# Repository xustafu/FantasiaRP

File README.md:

# FantasiaRP
Fantasia para RP2350B

## Installation Steps:  

  * Install free [VSCode](https://code.visualstudio.com/download).  
  * Add the free [PlatformIO extension](https://marketplace.visualstudio.com/items?itemName=platformio.platformio-ide). 
  * Download this repo
  * Open it up with VSCode
  * Click the platformio compile + upload button
  * That's it!

Change pin numbers for Serial(UART), SPI, Wire(i2c...) and LED(pixels)  in your pins_arduino.h file.  
In utils.hpp, initialize objects, some of them need pins numbers like 7Segment or buttons.  
Enjoy :)

## Pony Env (Beta 3) pin map

Traced from `RP2350B+PCM5100_Template/B3Kicad/Pony_env_B3.kicad_sch`. All definitions live in `src/utils.hpp`.

| Control | GPIO | Notes |
|---|---|---|
| ATTACK slider + CV | 47 (A7) | analog, inverting summing stage |
| DECAY slider + CV | 46 (A6) | analog |
| SPEED pot + LVL CV | 45 (A5) | analog |
| TRIGG in | 12 | inverted by Q7, external pull-up |
| EOC out | 18 | inverted by Q1 (GPIO LOW = jack high) |
| Trigger button | 44 | to GND when pressed (`INPUT_PULLUP`) |
| Button NeoPixel | 43 | 1 pixel |
| MODE 1-4 | 42, 41, 40, 33 | switch common = 3.3V, active HIGH |
| SHAPE 1-4 | 35, 34, 31, 37 | active HIGH |
| RANGE 1-4 | 19, 39, 38, 36 | active HIGH |
| I2S BCK / LRCK / DIN | 0 / 1 / 2 | PCM5100: L = ENV out, R = ENV_ATTE out |

Output scaling: about -9.49 V at the jack per 1.0 DAC full scale (inverted). Use `jackVoltsToDac()` to set values in jack volts.

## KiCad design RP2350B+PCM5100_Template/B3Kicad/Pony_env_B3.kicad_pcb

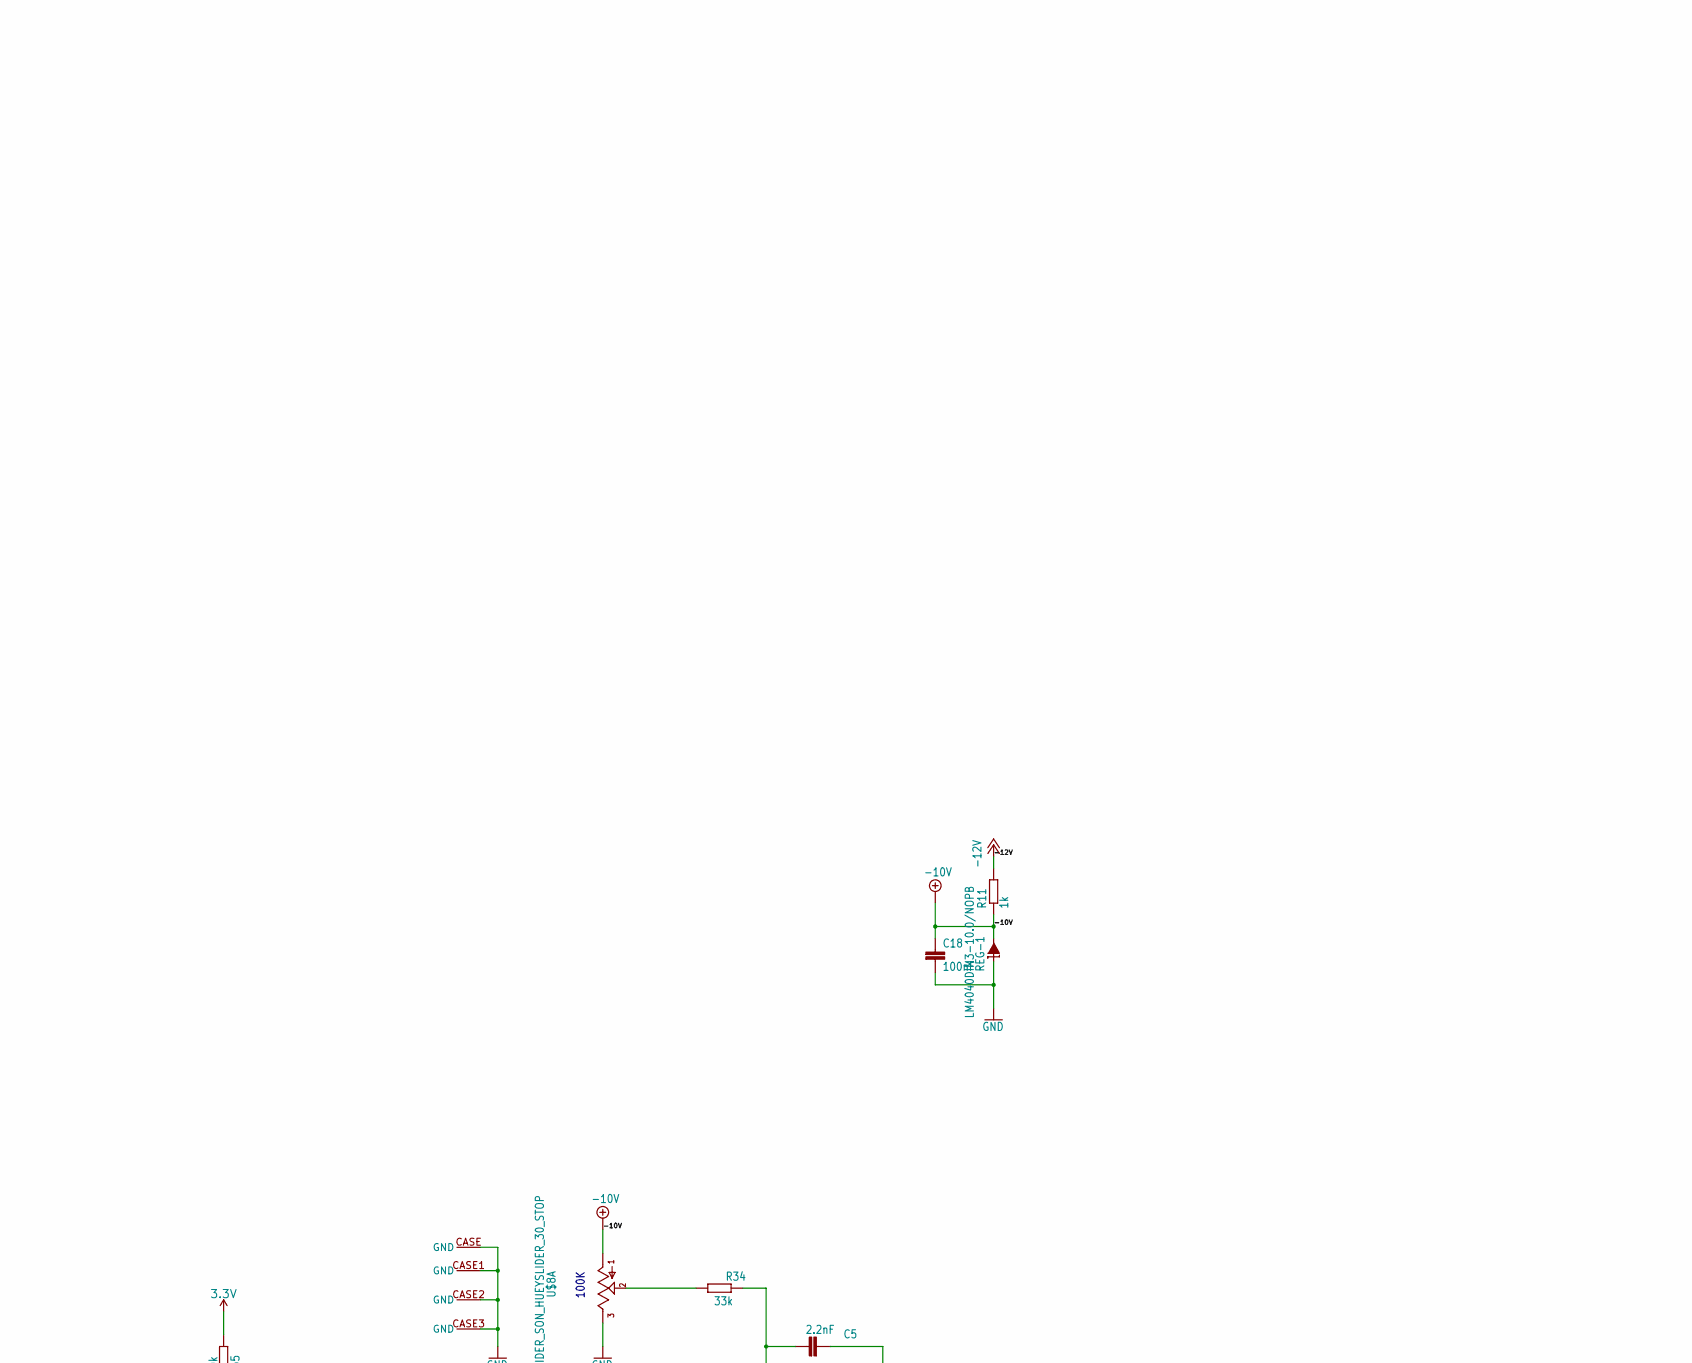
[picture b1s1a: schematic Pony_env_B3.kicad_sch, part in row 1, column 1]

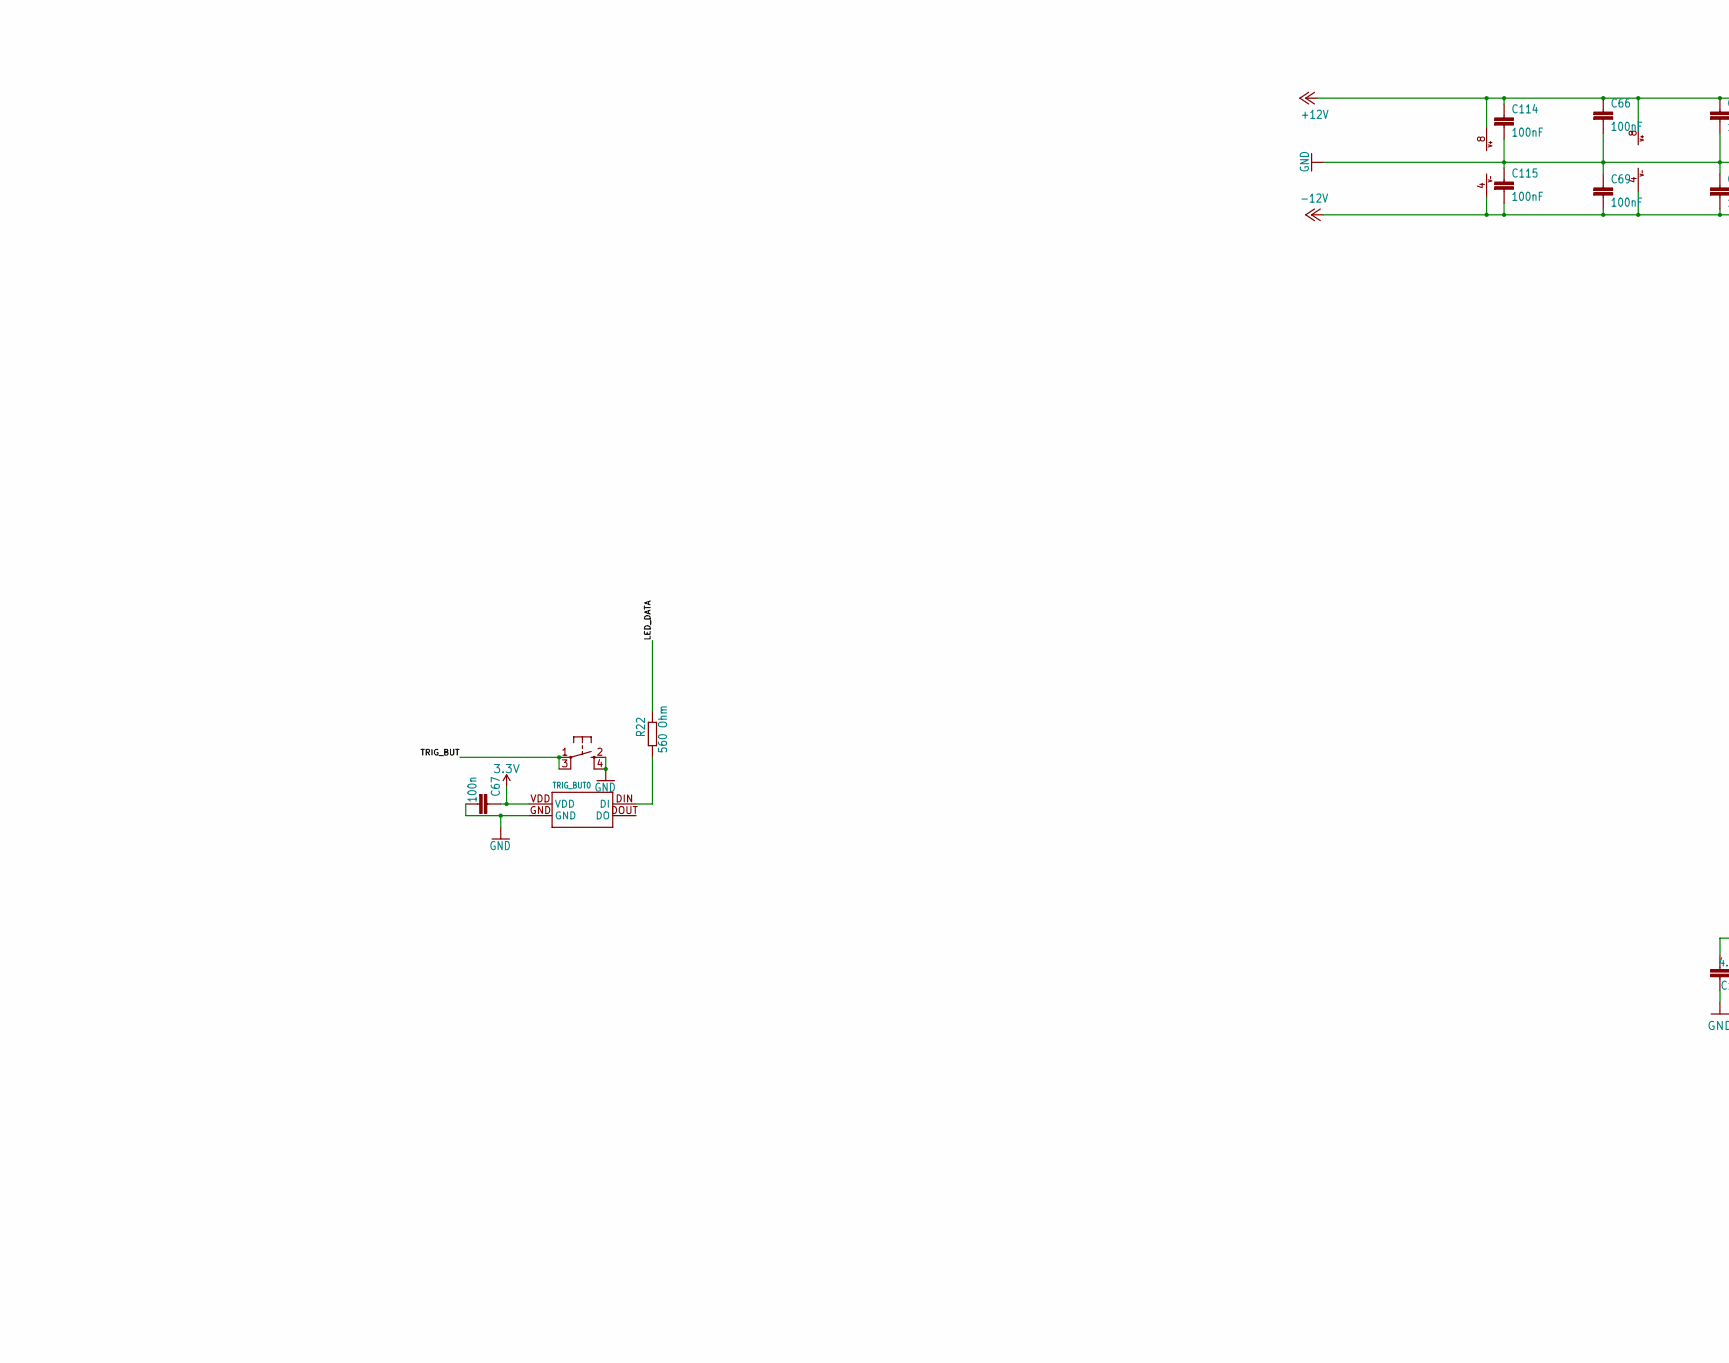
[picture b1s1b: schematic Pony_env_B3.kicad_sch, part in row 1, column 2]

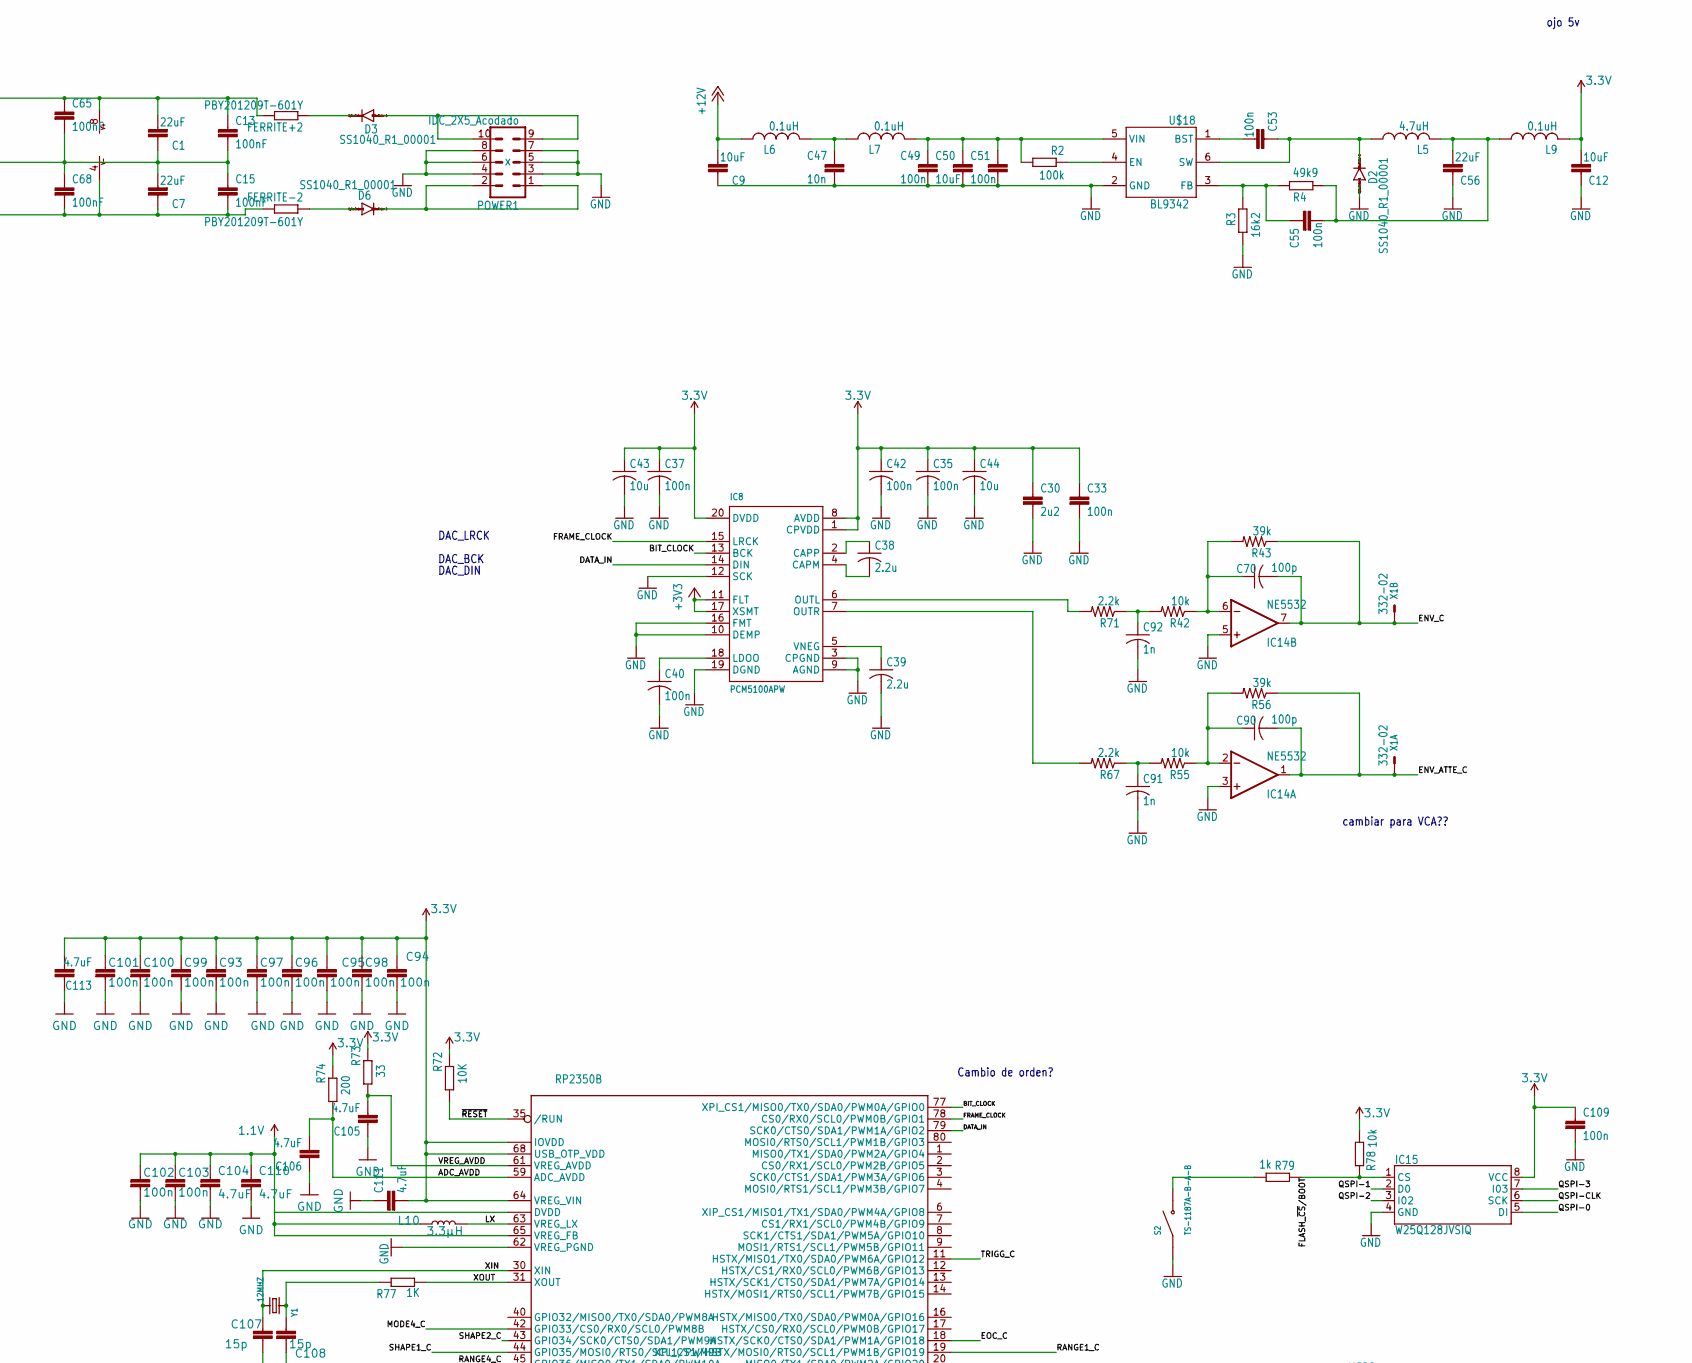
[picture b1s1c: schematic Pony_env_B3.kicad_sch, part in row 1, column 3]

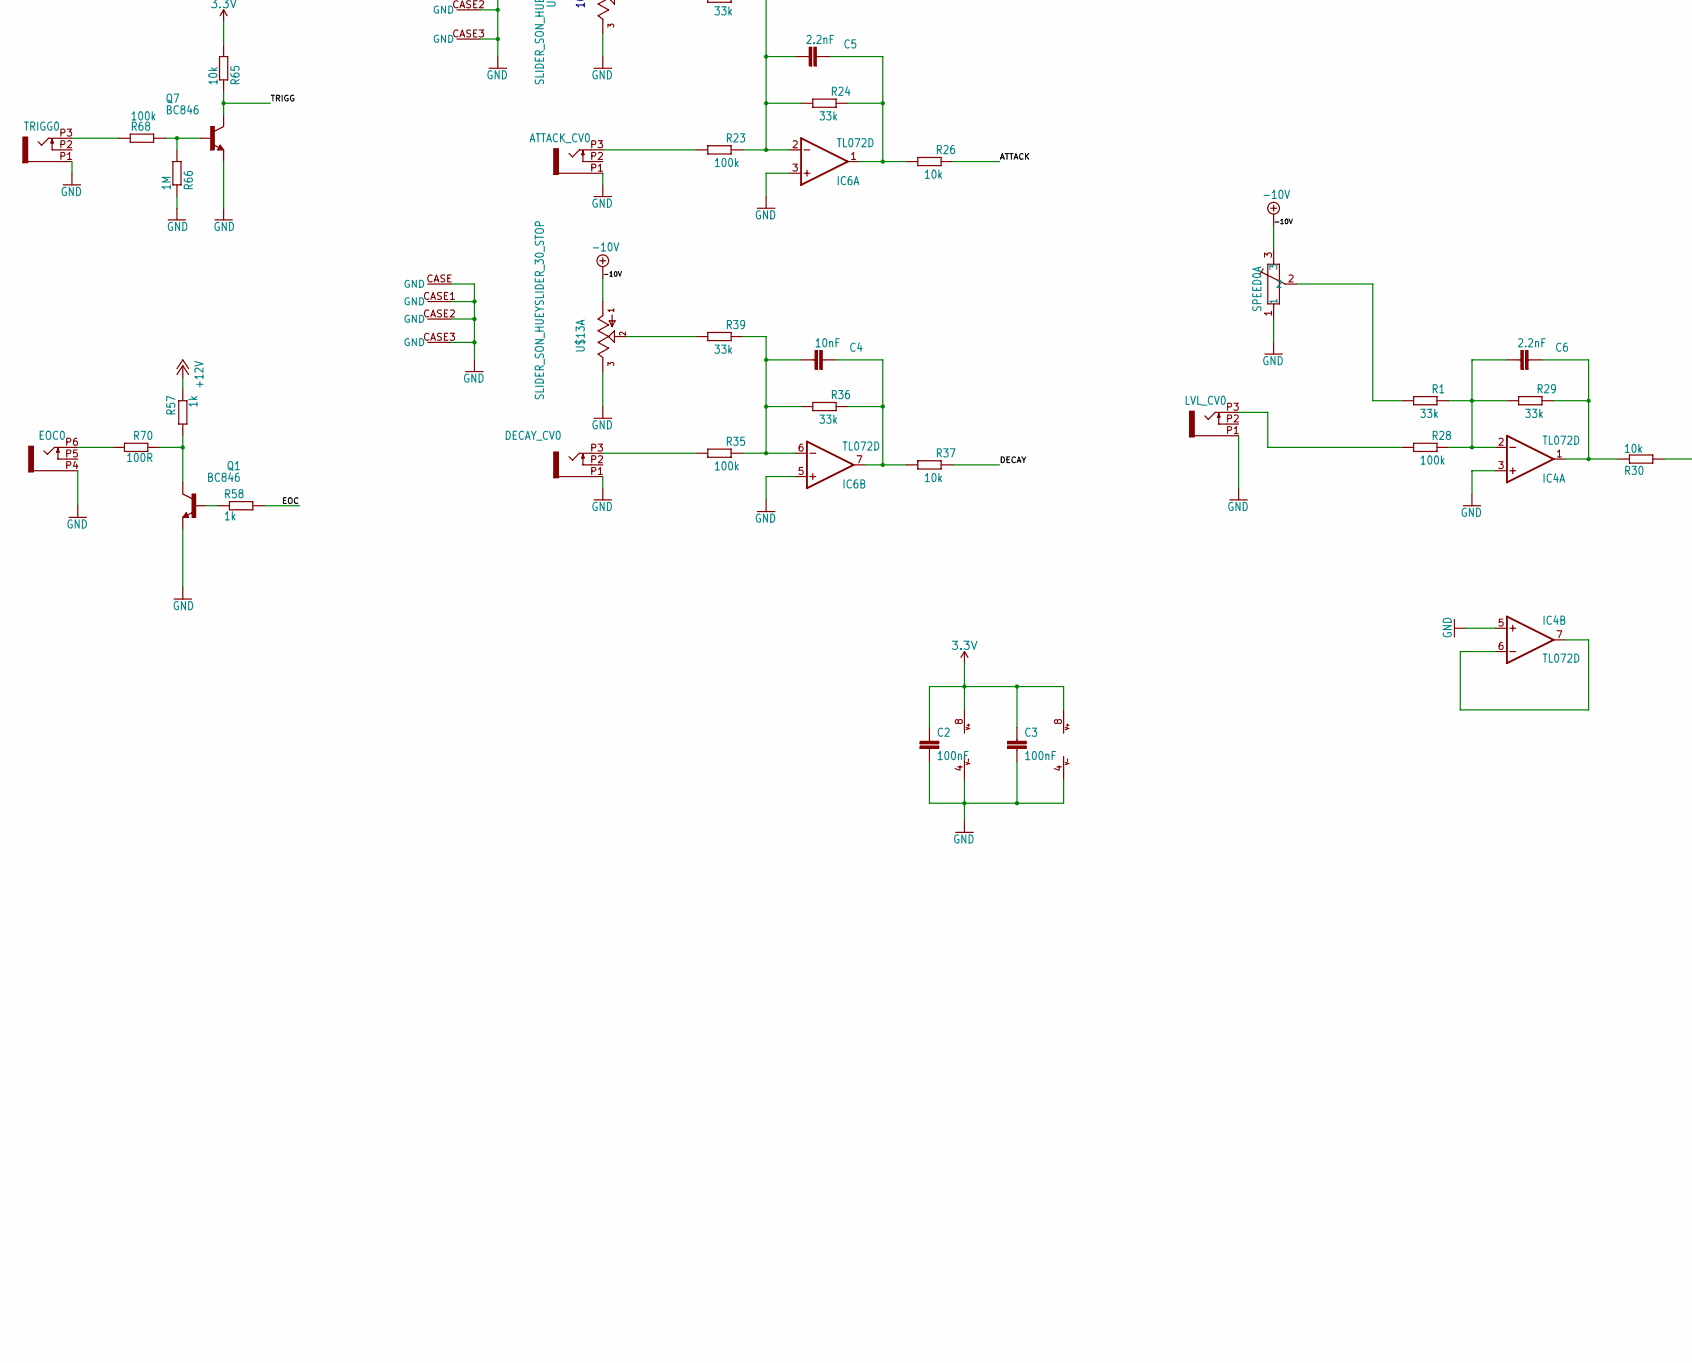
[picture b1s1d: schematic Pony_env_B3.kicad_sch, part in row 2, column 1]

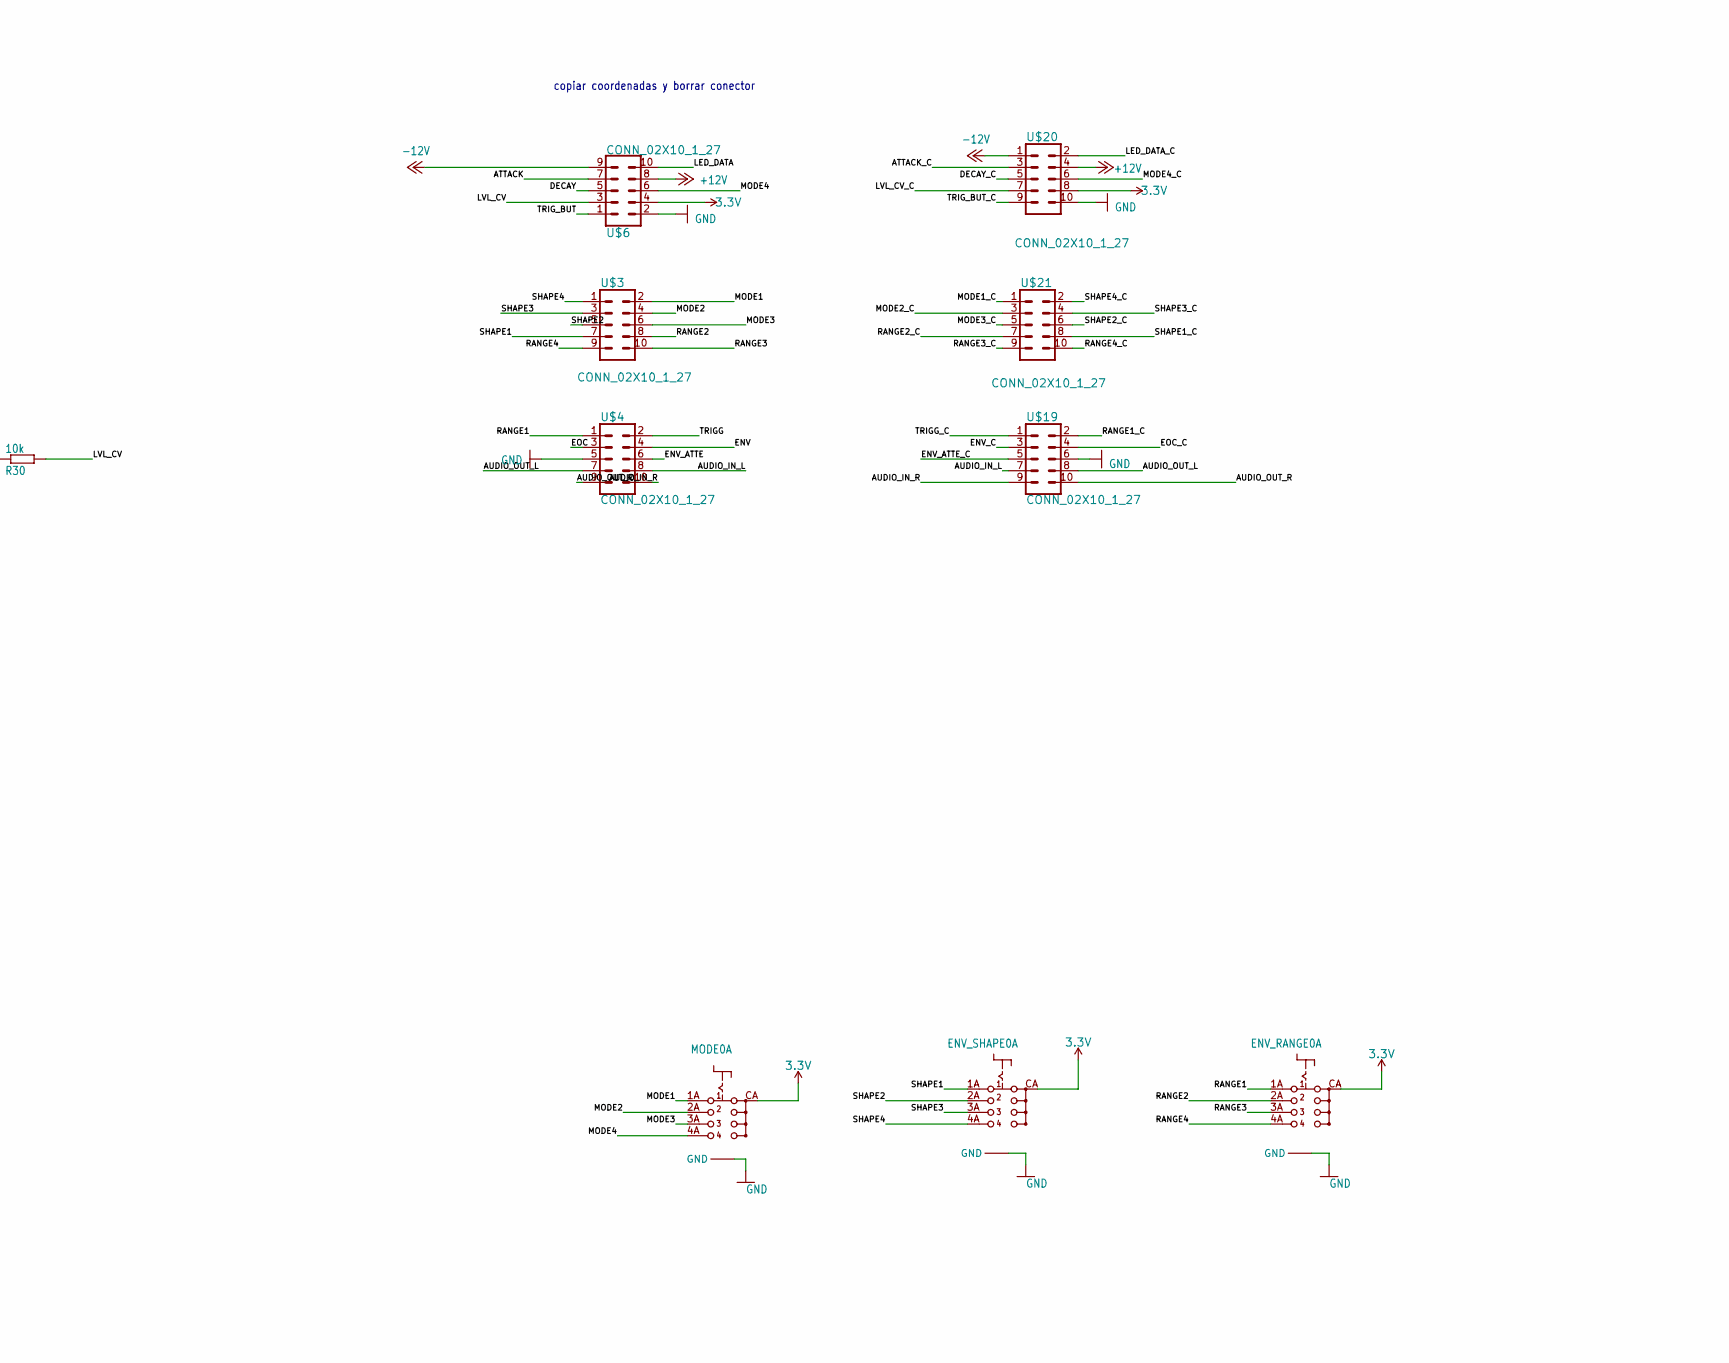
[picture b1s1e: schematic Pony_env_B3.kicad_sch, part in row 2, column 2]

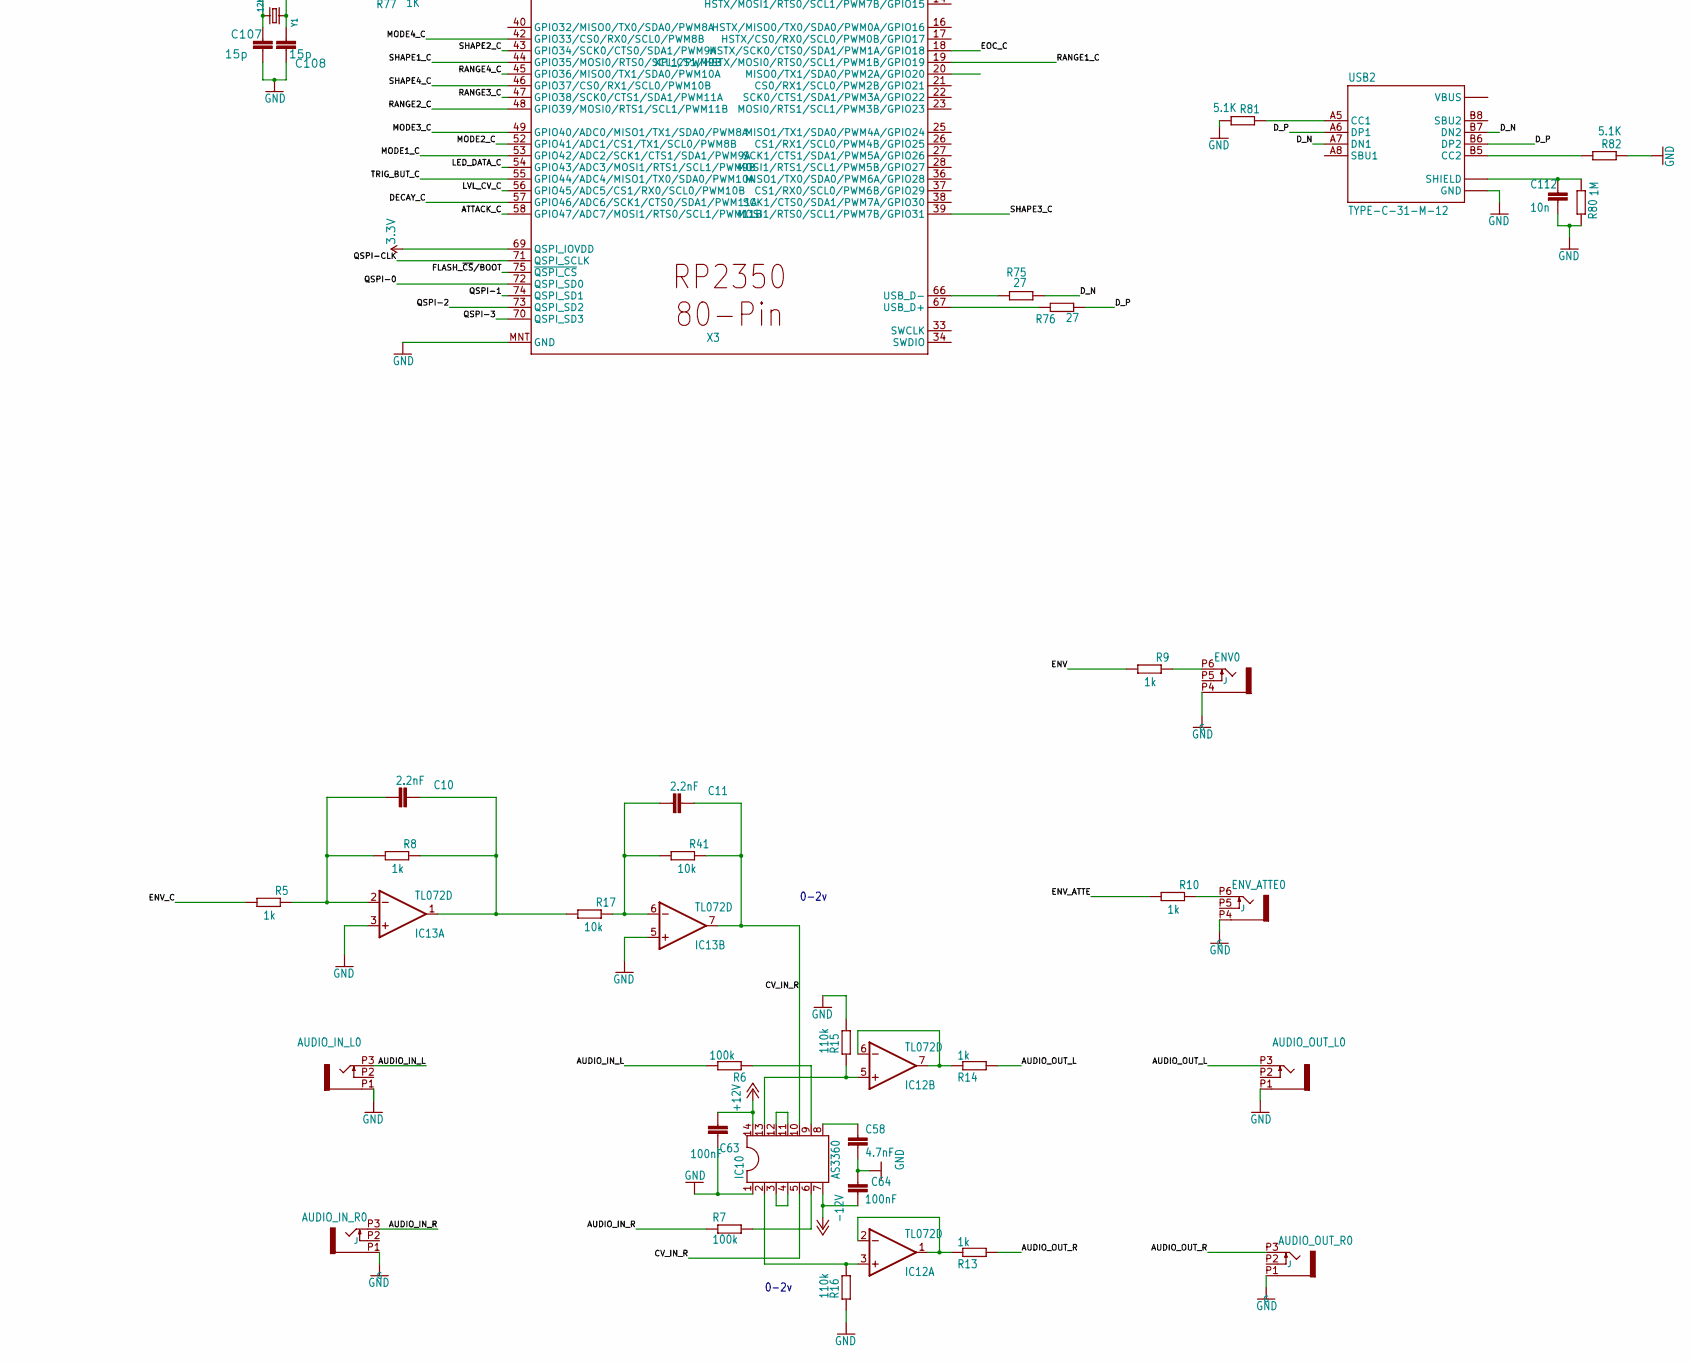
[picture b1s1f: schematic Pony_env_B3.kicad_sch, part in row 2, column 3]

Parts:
ATTACK_CV0: OG-PJ301_PJ301_THONKICONNNOHOLE_IZQ; NOHOLER_GND_SHORT_RIGHT
AUDIO_IN_L0: OG-PJ301_PJ301_THONKICONNNOHOLE_IZQ; NOHOLER_GND_SHORT_RIGHT
AUDIO_IN_R0: OG-PJ301_PJ301_THONKICONNNOHOLE_IZQ; NOHOLER_GND_SHORT_RIGHT
AUDIO_OUT_L0: OG-PJ301_PJ301_THONKICONNNOHOLE_IZQ; NOHOLER_GND_SHORT_RIGHT
AUDIO_OUT_R0: OG-PJ301_PJ301_THONKICONNNOHOLE_IZQ; NOHOLER_GND_SHORT_RIGHT
C1, C7, C56: 22uF; C0805
C2, C3, C13, C15, C18, C63, C64, C65, C66, C68, C69, C114, C115: 100nF; C0603
C4: 10nF; C0603
C5, C6, C10, C11: 2.2nF; C0603
C9, C12: 10uF; C0805
C30: 2u2; C0603
C33, C35, C37, C40, C42, C49, C51, C53, C55, C67, C109: 100n; C0603
C38, C39: 2.2u; C0805
C43, C44: 10u; C0603
C47, C112: 10n; C0603
C50: 10uF; C0603
C58: 4.7nF; C0603
C70, C90: 100p; C0603
C91, C92: 1n; C0603
C93, C94, C95, C96, C97, C98, C99, C100, C101, C102, C103: 100n; 0603
C104, C110: 4.7uF; 0603
C105, C106, C111: 4.7uF; C0805
C107, C108: 15p; 0603
C113: 4.7uF; C0603
D2, D3, D6: SS1040_R1_00001; SOD123
DECAY_CV0: OG-PJ301_PJ301_THONKICONNNOHOLE_IZQ; NOHOLER_GND_SHORT_RIGHT
ENV0: OG-PJ301_PJ301_THONKICONNNOHOLE_IZQ; NOHOLE_RIG
ENV_ATTE0: OG-PJ301_PJ301_THONKICONNNOHOLE_IZQ; NOHOLE_RIG
ENV_RANGE0: SLIDE_SWITCH_DP4TMINI; SLIDE_SWITCH_DP4T_MINI
ENV_SHAPE0: SLIDE_SWITCH_DP4TMINI; SLIDE_SWITCH_DP4T_MINI
EOC0: OG-PJ301_PJ301_THONKICONNNOHOLE_IZQ; NOHOLE_RIG
FERRITE+2: PBY201209T-601Y; R0603
FERRITE-2: PBY201209T-601Y; R0603
IC4, IC6, IC12, IC13: TL072D; SO08
IC8: PCM5100APW; SSOP20
IC10: AS3360; SO14
IC14: NE5532; SO08
IC15: W25Q128JVSIQ; SOIC-8
L5: 4.7uH; L3225P
L6, L7, L9: 0.1uH; C0805
L10: 3.3μH; 1008(2520)
LVL_CV0: OG-PJ301_PJ301_THONKICONNNOHOLE_IZQ; NOHOLER_GND_SHORT_RIGHT
MODE0: SLIDE_SWITCH_DP4TMINI; SLIDE_SWITCH_DP4T_MINI
POWER1: IDC_2X5_Acodado; 2X5-POWER_ACODADO
Q1, Q7: BC846; SOT23
R1, R24, R29, R34, R36, R39: 33k; R0603
R2, R23, R28, R35, R68: 100k; R0603
R3: 16k2; R0603
R4: 49k9; R0603
R5, R8, R9, R10, R11, R13, R14, R57, R58, R79: 1k; R0603
R6, R7: 100k; R0603; MOUSER 71-CRCW0603-3.3K-E3
R15, R16: 110k; R0603
R17, R26, R30, R37, R41, R42, R55, R65, R78: 10k; R0603
R22: 560 Ohm; R0603
R43, R56: 39k; R0603
R66, R80: 1M; R0603
R67, R71: 2.2k; R0603
R70: 100R; R0603
R72: 10K; R0603
R73: 33; R0603
R74: 200; R0603
R75, R76: 27; R0603
R77: 1K; R0603
R81, R82: 5.1K; R0603
REG-1: LM4040DIM3-10.0/NOPB; DBZ_R-PDSO-G3
S2: TS-1187A-B-A-B; SW_TS-1187A-B-A-B
SPEED0: 10k; POT-ALPS-RK09L1140_SMALL_MOVE_GND
TRIGG0: OG-PJ301_PJ301_THONKICONNNOHOLE_IZQ; NOHOLER_GND_SHORT_RIGHT
TRIG_BUT0: BUTTON_NEOPIXELBUTTON_PIXEL_ç; BUTTON_PIXEL_ç
U$3, U$4, U$6, U$19, U$20, U$21: CONN_02X10_1_27; 2X5-SMD-UNSHROUDED
U$8, U$13: SLIDER_SON_HUEYSLIDER_30_STOP; SLIDER_30_STOP
U$18: BL9342; SOT23-6
USB2: TYPE-C-31-M-12; HRO_TYPE-C-31-M-12
X1: 332-02
X3: RP2350B; QFN80
Y1: 12MHZ; CRYSTAL_3.2X2.5

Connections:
1.1V: C102.1, C103.1, C104.1, C110.1, L10.1, X3.10 (DVDD), X3.32 (DVDD), X3.51 (DVDD), X3.65 (VREG_FB)
3.3V: C2.1, C3.1, C12.2, C30.1, C33.1, C35.1, C37.1, C42.1, C43.1, C44.1, C67.1, C93.1, C94.1, C95.1, C96.1, C97.1, C98.1, C99.1, C100.1, C101.1, C109.1, C111.2, C113.2, ENV_RANGE0.CA, ENV_SHAPE0.CA, IC4.8 (V+), IC6.8 (V+), IC8.1 (CPVDD), IC8.8 (AVDD), IC8.20 (DVDD), IC15.8 (VCC), L9.2, MODE0.CA, R65.2, R72.2, R73.2, R74.2, R78.2, TRIG_BUT0.VDD, U$6.4, U$20.8, X3.5 (IOVDD), X3.15 (IOVDD), X3.24 (IOVDD), X3.29 (IOVDD), X3.41 (IOVDD), X3.50 (IOVDD), X3.60 (IOVDD), X3.64 (VREG_VIN), X3.68 (USB_OTP_VDD), X3.69 (QSPI_IOVDD), X3.76 (IOVDD)
+3V3: IC8.11 (FLT), IC8.17 (XSMT)
+12V: C1.2, C9.2, C13.1, C63.1, C65.1, C66.1, C114.1, FERRITE+2.2, IC10.14, IC12.8 (V+), IC13.8 (V+), IC14.8 (V+), L6.1, R57.1, U$6.8, U$20.4
-10V: C18.1, R11.1, REG-1.2 (A), SPEED0.3, U$8.1, U$13.1
-12V: C7.1, C15.2, C64.1, C68.2, C69.2, C115.2, FERRITE-2.2, IC10.7, IC12.4 (V-), IC13.4 (V-), IC14.4 (V-), R11.2, U$6.9, U$20.1
/ADC_AVDD: C106.2, R74.1, X3.59 (ADC_AVDD)
/ATTACK: R26.2, U$6.7
/ATTACK_C: U$20.3, X3.58 (GPIO47/ADC7/MOSI1/RTS0/SCL1/PWM11B)
/AUDIO_IN_L: AUDIO_IN_L0.P3 (3), R6.2, U$4.8, U$19.7
/AUDIO_IN_R: AUDIO_IN_R0.P3 (3), R7.1, U$4.10, U$19.9
/AUDIO_OUT_L: AUDIO_OUT_L0.P3 (3), R14.2, U$4.7, U$19.8
/AUDIO_OUT_R: AUDIO_OUT_R0.P3 (3), R13.2, U$4.9, U$19.10
/BIT_CLOCK: IC8.13 (BCK), X3.77 (XPI_CS1/MISO0/TX0/SDA0/PWM0A/GPIO0)
/CV_IN_R: C11.2, IC10.5, IC10.10, IC13.7 (OUT), R41.2
/DATA_IN: IC8.14 (DIN), X3.79 (SCK0/CTS0/SDA1/PWM1A/GPIO2)
/DECAY: R37.2, U$6.5
/DECAY_C: U$20.5, X3.57 (GPIO46/ADC6/SCK1/CTS0/SDA1/PWM11A)
/D_N: R75.1, USB2.A7 (DN1), USB2.B7 (DN2)
/D_P: R76.1, USB2.A6 (DP1), USB2.B6 (DP2)
/ENV: R9.1, U$4.4
/ENV_ATTE: R10.1, U$4.6
/ENV_ATTE_C: C90.2, IC14.1 (OUT), R56.1, U$19.5, X1.1 (S)
/ENV_C: C70.2, IC14.7 (OUT), R5.1, R43.1, U$19.3, X1.2 (S)
/EOC: R58.2, U$4.3
/EOC_C: U$19.4, X3.18 (HSTX/SCK0/CTS0/SDA1/PWM1A/GPIO18)
/FLASH_~CS/BOOT: IC15.1 (CS), R78.1, R79.1, X3.75 (~QSPI_CS)
/FRAME_CLOCK: IC8.15 (LRCK), X3.78 (CS0/RX0/SCL0/PWM0B/GPIO1)
/LED_DATA: R22.1, U$6.10
/LED_DATA_C: U$20.2, X3.54 (GPIO43/ADC3/MOSI1/RTS1/SCL1/PWM9B)
/LVL_CV: R30.2, U$6.3
/LVL_CV_C: U$20.7, X3.56 (GPIO45/ADC5/CS1/RX0/SCL0/PWM10B)
/LX: L10.2, X3.63 (VREG_LX)
/MODE1: MODE0.1A (1), U$3.2
/MODE1_C: U$21.1, X3.53 (GPIO42/ADC2/SCK1/CTS1/SDA1/PWM9A)
/MODE2: MODE0.2A (2), U$3.4
/MODE2_C: U$21.3, X3.52 (GPIO41/ADC1/CS1/TX1/SCL0/PWM8B)
/MODE3: MODE0.3A (3), U$3.6
/MODE3_C: U$21.5, X3.49 (GPIO40/ADC0/MISO1/TX1/SDA0/PWM8A)
/MODE4: MODE0.4A (4), U$6.6
/MODE4_C: U$20.6, X3.42 (GPIO33/CS0/RX0/SCL0/PWM8B)
/QSPI-0: IC15.5 (DI), X3.72 (QSPI_SD0)
/QSPI-1: IC15.2 (D0), X3.74 (QSPI_SD1)
/QSPI-2: IC15.3 (I02), X3.73 (QSPI_SD2)
/QSPI-3: IC15.7 (I03), X3.70 (QSPI_SD3)
/QSPI-CLK: IC15.6 (SCK), X3.71 (QSPI_SCLK)
/RANGE1: ENV_RANGE0.1A (1), U$4.1
/RANGE1_C: U$19.2, X3.19 (XPI_CS1/HSTX/MOSI0/RTS0/SCL1/PWM1B/GPIO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)
/RANGE2: ENV_RANGE0.2A (2), U$3.8
/RANGE2_C: U$21.7, X3.48 (GPIO39/MOSI0/RTS1/SCL1/PWM11B)
/RANGE3: ENV_RANGE0.3A (3), U$3.10
/RANGE3_C: U$21.9, X3.47 (GPIO38/SCK0/CTS1/SDA1/PWM11A)
/RANGE4: ENV_RANGE0.4A (4), U$3.9
/RANGE4_C: U$21.10, X3.45 (GPIO36/MISO0/TX1/SDA0/PWM10A)
/SHAPE1: ENV_SHAPE0.1A (1), U$3.7
/SHAPE1_C: U$21.8, X3.44 (GPIO35/MOSI0/RTS0/SCL1/PWM9B)
/SHAPE2: ENV_SHAPE0.2A (2), U$3.5
/SHAPE2_C: U$21.6, X3.43 (GPIO34/SCK0/CTS0/SDA1/PWM9A)
/SHAPE3: ENV_SHAPE0.3A (3), U$3.3
/SHAPE3_C: U$21.4, X3.39 (MOSI1/RTS0/SCL1/PWM7B/GPIO31)
/SHAPE4: ENV_SHAPE0.4A (4), U$3.1
/SHAPE4_C: U$21.2, X3.46 (GPIO37/CS0/RX1/SCL0/PWM10B)
/TRIGG: Q7.3 (C), R65.1, U$4.2
/TRIGG_C: U$19.1, X3.11 (HSTX/MISO1/TX0/SDA0/PWM6A/GPIO12)
/TRIG_BUT: TRIG_BUT0.1, TRIG_BUT0.3, U$6.1
/TRIG_BUT_C: U$20.9, X3.55 (GPIO44/ADC4/MISO1/TX0/SDA0/PWM10A)
/VREG_AVDD: C105.2, R73.1, X3.61 (VREG_AVDD)
/XIN: C107.1, X3.30 (XIN), Y1.1
/XOUT: R77.1, X3.31 (XOUT)
/~RESET: R72.1, X3.35 (/RUN)
GND: ATTACK_CV0.P1 (1), AUDIO_IN_L0.P1 (1), AUDIO_IN_R0.P1 (1), AUDIO_OUT_L0.P1 (1), AUDIO_OUT_R0.P1 (1), C1.1, C2.2, C3.2, C7.2, C9.1, C12.1, C13.2, C15.1, C18.2, C30.2, C33.2, C35.2, C37.2, C39.2, C40.2, C42.2, C43.2, C44.2, C47.2, C49.2, C50.2, C51.2, C56.1, C58.2, C63.2, C64.2, C65.2, C66.2, C67.2, C68.1, C69.1, C91.2, C92.2, C93.2, C94.2, C95.2, C96.2, C97.2, C98.2, C99.2, C100.2, C101.2, C102.2, C103.2, C104.2, C105.1, C106.1, C107.2, C108.2, C109.2, C110.2, C111.1, C112.2, C113.1, C114.2, C115.1, D2.A, DECAY_CV0.P1 (1), ENV0.P4 (1), ENV_ATTE0.P4 (1), ENV_RANGE0.PLATE_A (GND), ENV_RANGE0.PLATE_B (GND), ENV_SHAPE0.PLATE_A (GND), ENV_SHAPE0.PLATE_B (GND), EOC0.P4 (1), IC4.3 (+IN), IC4.4 (V-), IC4.5 (+IN), IC6.3 (+IN), IC6.4 (V-), IC6.5 (+IN), IC8.3 (CPGND), IC8.9 (AGND), IC8.10 (DEMP), IC8.12 (SCK), IC8.16 (FMT), IC8.19 (DGND), IC10.1, IC13.3 (+IN), IC13.5 (+IN), IC14.3 (+IN), IC14.5 (+IN), IC15.4 (GND), LVL_CV0.P1 (1), MODE0.PLATE_A (GND), MODE0.PLATE_B (GND), POWER1.3, POWER1.4, POWER1.5, POWER1.6, POWER1.7, POWER1.8, Q1.2 (E), Q7.2 (E), R3.1, R15.1, R16.2, R66.1, R80.1, R81.2, R82.1, REG-1.1 (C), S2.A (COM), S2.B (COM), SPEED0.1, TRIGG0.P1 (1), TRIG_BUT0.2, TRIG_BUT0.4, TRIG_BUT0.GND, U$4.5, U$6.2, U$8.3, U$8.CASE (GND), U$8.CASE1 (GND), U$8.CASE2 (GND), U$8.CASE3 (GND), U$13.3, U$13.CASE (GND), U$13.CASE1 (GND), U$13.CASE2 (GND), U$13.CASE3 (GND), U$18.2 (GND), U$19.6, U$20.10, USB2.A1_B12 (GND), USB2.B1_A12 (GND), X3.62 (VREG_PGND), X3.MNT (GND)
unnamed: ATTACK_CV0.P3 (3), R23.1
unnamed: C47.1, L6.2, L7.1
unnamed: C55.2, C56.2, L5.2, L9.1, R4.1
unnamed: C58.1, IC10.8
unnamed: C91.1, R55.2, R67.1
unnamed: C92.1, R42.2, R71.1
unnamed: C108.1, R77.2, Y1.2
unnamed: C112.1, R80.2, USB2.S1 (SHIELD), USB2.S2 (SHIELD), USB2.S3 (SHIELD), USB2.S4 (SHIELD)
unnamed: D3.A, POWER1.9, POWER1.10
unnamed: D3.C, FERRITE+2.1
unnamed: D6.A, FERRITE-2.1
unnamed: D6.C, POWER1.1, POWER1.2
unnamed: DECAY_CV0.P3 (3), R35.1
unnamed: ENV0.P6 (3), R9.2
unnamed: ENV_ATTE0.P6 (3), R10.2
unnamed: EOC0.P6 (3), R70.2
unnamed: C6.1, IC4.2 (-IN), R1.2, R28.2, R29.1
unnamed: C6.2, IC4.1 (OUT), R29.2, R30.1
unnamed: IC4.6 (-IN), IC4.7 (OUT)
unnamed: C5.1, IC6.2 (-IN), R23.2, R24.1, R34.2
unnamed: C5.2, IC6.1 (OUT), R24.2, R26.1
unnamed: C4.1, IC6.6 (-IN), R35.2, R36.1, R39.2
unnamed: C4.2, IC6.7 (OUT), R36.2, R37.1
unnamed: C38.2, IC8.4 (CAPM)
unnamed: C38.1, IC8.2 (CAPP)
unnamed: C40.1, IC8.18 (LDOO)
unnamed: IC8.6 (OUTL), R71.2
unnamed: IC8.7 (OUTR), R67.2
unnamed: C39.1, IC8.5 (VNEG)
unnamed: IC10.3, IC10.4
unnamed: IC10.6, R7.2
unnamed: IC10.9, R6.1
unnamed: IC10.11, IC10.12
unnamed: IC10.2, IC12.3 (+IN), R16.1
unnamed: IC12.1 (OUT), IC12.2 (-IN), R13.1
unnamed: IC10.13, IC12.5 (+IN), R15.2
unnamed: IC12.6 (-IN), IC12.7 (OUT), R14.1
unnamed: C10.1, IC13.2 (-IN), R5.2, R8.1
unnamed: C10.2, IC13.1 (OUT), R8.2, R17.1
unnamed: C11.1, IC13.6 (-IN), R17.2, R41.1
unnamed: C90.1, IC14.2 (-IN), R55.1, R56.2
unnamed: C70.1, IC14.6 (-IN), R42.1, R43.2
unnamed: LVL_CV0.P3 (3), R28.1
unnamed: Q1.1 (B), R58.1
unnamed: Q1.3 (C), R57.2, R70.1
unnamed: Q7.1 (B), R66.2, R68.1
unnamed: R1.1, SPEED0.2
unnamed: R34.1, U$8.2
unnamed: R39.1, U$13.2
unnamed: R79.2, S2.C (NO), S2.D (NO)
unnamed: R68.2, TRIGG0.P3 (3)
unnamed: R22.2, TRIG_BUT0.DIN (DI)
unnamed: C53.2, U$18.1 (BST)
unnamed: R2.2, U$18.4 (EN)
unnamed: C55.1, R3.2, R4.2, U$18.3 (FB)
unnamed: C53.1, D2.C, L5.1, U$18.6 (SW)
unnamed: C49.1, C50.1, C51.1, L7.2, R2.1, U$18.5 (VIN)
unnamed: R81.1, USB2.A5 (CC1)
unnamed: R82.2, USB2.B5 (CC2)
unnamed: USB2.A4_B9 (VBUS), USB2.B4_A9 (VBUS)
unnamed: R76.2, X3.67 (USB_D+)
unnamed: R75.2, X3.66 (USB_D-)

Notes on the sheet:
Cambio de orden?
copiar coordenadas y borrar conector
0-2v
cambiar para VCA??
ojo 5v
DAC_LRCK
DAC_DIN
DAC_BCK
100K

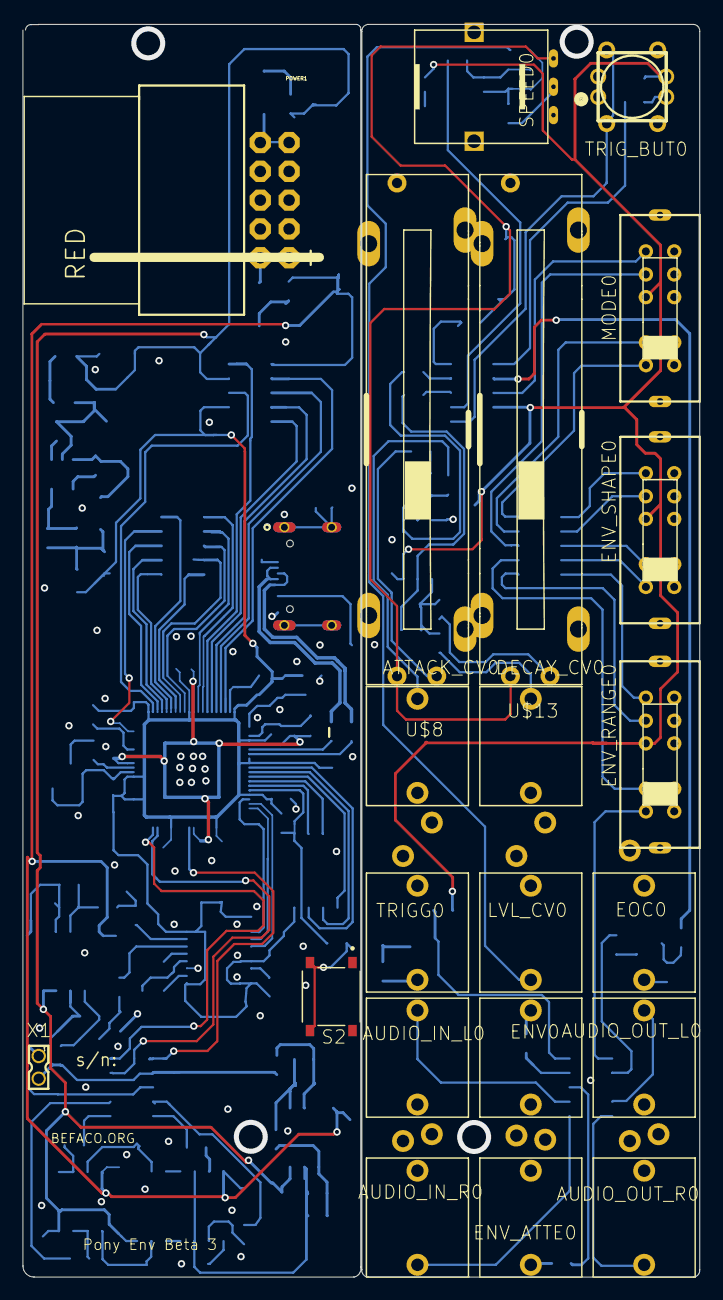
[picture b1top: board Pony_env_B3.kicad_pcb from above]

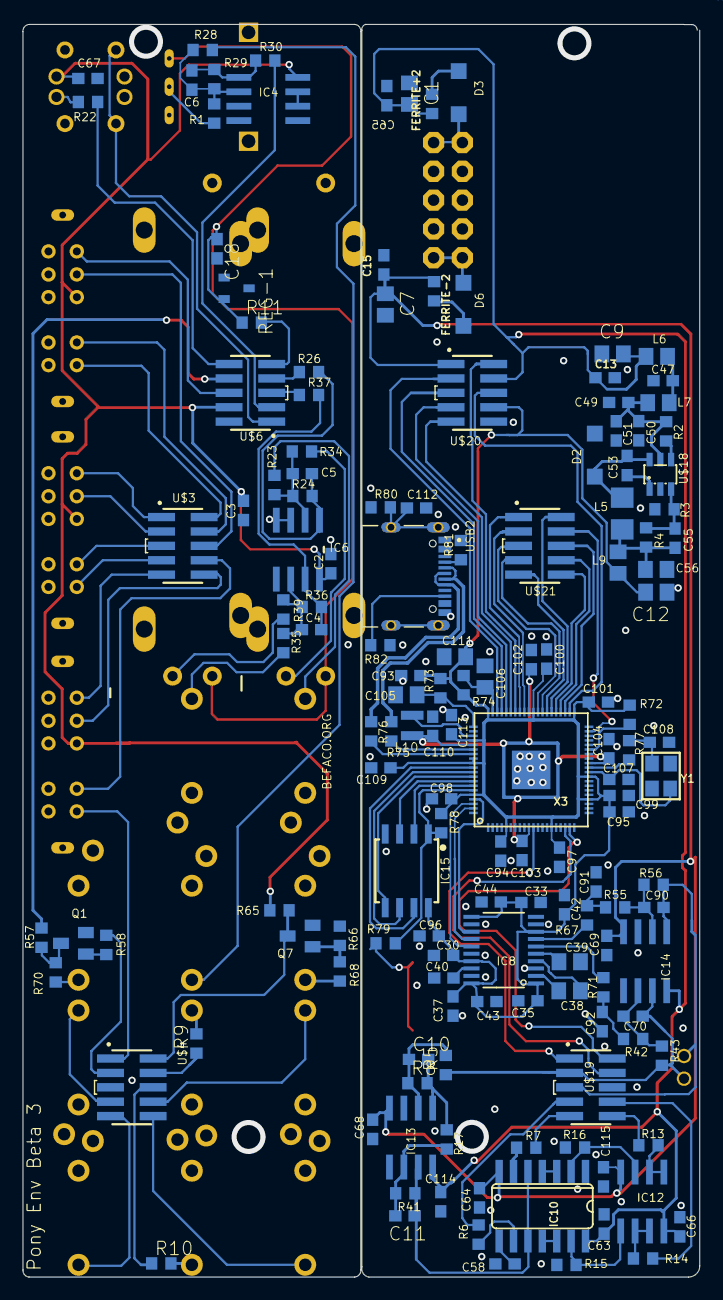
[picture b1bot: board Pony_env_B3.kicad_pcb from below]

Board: 2 copper layers, 59.7 x 110.5 mm, 170 parts (149 on the bottom side), 133 nets.

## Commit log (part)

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2025-09-23 Basic template
2025-09-23 added utils header for organization
2025-09-25 display, buttons, encoder WIP and audio test
2025-09-29 LEDs working
2025-09-29 easier to follow installation instructions
2026-02-28 Manu at Axolotl
2026-02-28 RP2350 at Axolot
2026-03-02 recommended extensions
2026-03-02 seven segment clearer
2026-03-02 buttons and clearer pixels
2026-03-03 files reorga
2026-05-25 changes to pins
2026-06-12 Update README with pin configuration instructions
    Add instructions for changing pin numbers and initializing objects.
